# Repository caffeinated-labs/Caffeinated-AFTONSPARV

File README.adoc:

= Caffeinated AFTONSPARV

This small PCB replaces the original board inside your https://www.ikea.com/us/en/p/aftonsparv-led-decorative-light-planet-shape-multicolor-20559209/[AFTONSPARV Planet lamp].
It connects to your smart home setup via a common ESP32 firmware like https://esphome.io[esphome.io] or https://kno.wled.ge[WLED].

And the best thing, it's all OSHW certified: https://certification.oshwa.org/de000140.html[DE000140]

[#img-OSHW-DE000140,link=https://certification.oshwa.org/de000140.html]
image:docs/render.png[KiCad 3D render of the pcb, 500] image:docs/oshw.svg[OSHW-DE000140, 300]
image:docs/caffeinated-aftonsparv.jpg[Caffeinated AFTONSPARV, 850]

== Instructions

=== Step 1: Remove the cover
Remove the bottom cover from the AFTONSPARV lamp, there is no need to open the top cover. Open the marked screws, there's one under the sticker.

image:docs/step1.jpg[The bottom screws are highlited, 500]

=== Step 2: Disconnect the wires
Carefully de-solder all wires from the old board, it is not needed anymore.

image:docs/step2.jpg[Front of the lamp with the cover removed. The original pcb is visible, 500]

=== Step 3: Connect the PCB
Carefully solder the wires to the Caffeinated AFTONSPARV as shown below:

|===
| IKEA Lamp | PCB

|LED, black | LED R
|LED, green | LED G
|LED, transparent | LED B
|LED, white | LED {plus}

|Plug, white | POWER {plus}
|Plug, black | POWER -
|===
image:docs/pinout.png[LED and Power connections, 500]
image:docs/step3.jpg[All wires connected to the PCB, 500]

See <<PinOut>> for more details

=== Step 4: Test
Connect the power and test the PCB.
If nothing gets hot, you can measure 3.3V at the USB Port continue with the firmware installation

image:docs/step4.jpg[The PCB inside the lamp, 500]

=== Step 5: Install firmware
Connect the ESP to your computer using the TagConnect or USB interface and install the firmware of your choosing. The button on the front is connected to `IO9`, the boot-mode selectorfootnote:boot-mode[https://www.espressif.com/sites/default/files/documentation/esp32-c3-mini-1_datasheet_en.pdf#table.4].

IMPORTANT: The board *must* be powered with 24V to install firmware.

See <<Firmware>> and <<PinOut>> for more details

=== Step 6: Close it up
Carefully screw-on the cover and enjoy your new and _caffeinated_ lamp.

== PinOut

=== UART
NOTE: The diagram on the PCB v0.1 shows `IO8` - it is connected to `IO9`!

To upload software you can use the standard workflow using `esptool.py` footnote:esptool[https://docs.espressif.com/projects/esptool/en/latest/esp32/] just like any other ESP32 board. The UART interface is exposed on the TagConnect port:

image:docs/TagConnect.png[TagConnect location, 500] image:docs/TagConnect.svg[TagConnect pinout, 200]

It is recommended to use this https://github.com/Jana-Marie/USB-UART-BRIDGE[programmer from @Jana-Marie]

=== USB
In addition, the USB interface is exposed as well. It is located on the edge next to the 24V input. Please remember that the ESP32 uses 3.3V and *not* the usual 5V.

image:docs/USB-Interface.png[USB Interace, 500]

=== Boot Mode
The front button as well as the <<UART>> interface is connected to `IO9`, which is the boot mode selector (on older models `IO0`) on this ESP32footnote:boot-mode[]. Pressing the button or connecting it to ground puts the ESP into _Download Boot_ mode. Now you can install firmware via <<UART>> or <<USB>>

=== Power & LED
NOTE: On v0.1 the LEDs and Power connections are not labeled on the silkscreen.

Connect the AFTONSPARVs LEDs to the left ports as shown and the power input to the right most *big* connections, connecting to the USB Port will destroy the ESP.

image:docs/pinout.png[LED and Power connections, 500]

== Firmware
=== WLED
==== Installation
[%hardbreaks]
Installing the WLED firmware is easies with their web installer: https://install.wled.me/[install.wled.me]
When installing with `esptool` footnote:esptool[] follow this guide and use the ESP32-C3 binary: https://kno.wled.ge/basics/install-binary/[kno.wled.ge/basics/install-binary]
**Important:** Install this https://install.wled.me/bin/release_0_14_0/esp32-c3_bootloader_v2.bin[ESP32-C3 bootloader] *not* the ESP32 bootlader.

==== Configuration
[%hardbreaks]
LED Preferences > Hardware setup
*1*: `PWM RGB`
*Index*: `0`
*GPIOs*: `4`, `5`, `6`

*Button 0 GPIO*: `9`, `Pushbutton`

.Show screenshot
[%collapsible]
image:docs/wled.png[The above setting in the WLED interface, 400]

== Hardware

IMPORTANT: It is not possible to hand-solder this project, it requires a hot-air station or reflow oven. It is recommended to use a stencil for solder paste.

=== BOM

|===
| Reference         | Value                  | Qty | LCSC

|C1, C4, C7, C11    | 100nF                  | 4   | C14663
|C2                 | 100µF 35V              | 1   | C2831717
|C3, C6, C9, C10    | 4.7uF                  | 4   | C560882
|C5                 | 22pF                   | 1   | C105620
|L1                 | 10uH                   | 1   | C38117
|Q1-Q3              | AO3400A                | 3   | C347475
|R1-R3, R7-R10, R14 | 10kΩ                   | 8   | C98220
|R4-R6              | 20Ω                    | 3   | C22950
|R11                | 1Ω                     | 1   | C22936
|R12                | 100kΩ                  | 1   | C25803
|R13                | 22.1kΩ                 | 1   | C25961
|SW1                | SW_Push                | 1   | C2910748
|U1                 | ESP32-C3-MINI-1-[H/N]4 | 1   | C2934569 / C2838502
|U2                 | SY8201ABC              | 1   | C108052
|===

link:bom/ibom.html[BOM Tool]

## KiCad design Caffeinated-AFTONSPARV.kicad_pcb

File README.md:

# Caffeinated AFTONSPARV

This small PCB replaces the original board inside your [AFTONSPARV Planet lamp](https://www.ikea.com/us/en/p/aftonsparv-led-decorative-light-planet-shape-multicolor-20559209/).
You can connect it to your smart home using the ESP32 with common firmware. And the best thing, it's all OSHW certified: [DE000140](https://certification.oshwa.org/de000140.html)

## BOM
| Reference         | Value                  | Qty | LCSC                |
| ----------------- | ---------------------- | --- | ------------------- |
|C1, C4, C7, C11    | 100nF                  | 4   | C14663              |
|C2                 | 100µF 35V              | 1   | C2831717            |
|C3, C6, C9, C10    | 4.7uF                  | 4   | C560882             |
|C5                 | 22pF                   | 1   | C105620             |
|L1                 | 10uH                   | 1   | C38117              |
|Q1-Q3              | AO3400A                | 3   | C347475             |
|R1-R3, R7-R10, R14 | 10kΩ                   | 8   | C98220              |
|R4-R6              | 20Ω                    | 3   | C22950              |
|R11                | 1Ω                     | 1   | C22936              |
|R12                | 100kΩ                  | 1   | C25803              |
|R13                | 22.1kΩ                 | 1   | C25961              |
|SW1                | SW_Push                | 1   | C2910751            |
|U1                 | ESP32-C3-MINI-1-[H/N]4 | 1   | C2934569 / C2838502 |
|U2                 | SY8201ABC              | 1   | C108052             |

[BOM Tool](bom/ibom.html)

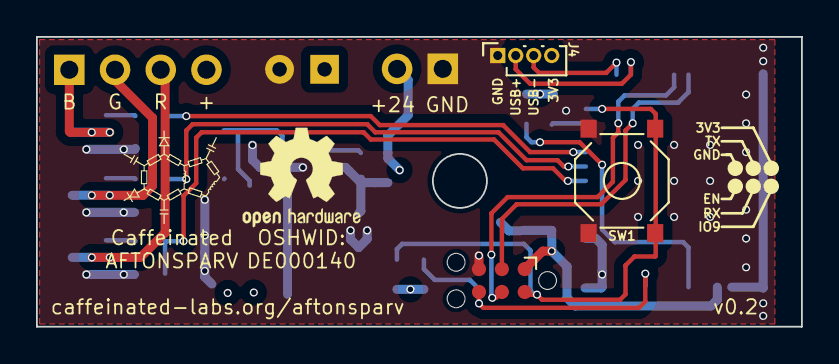
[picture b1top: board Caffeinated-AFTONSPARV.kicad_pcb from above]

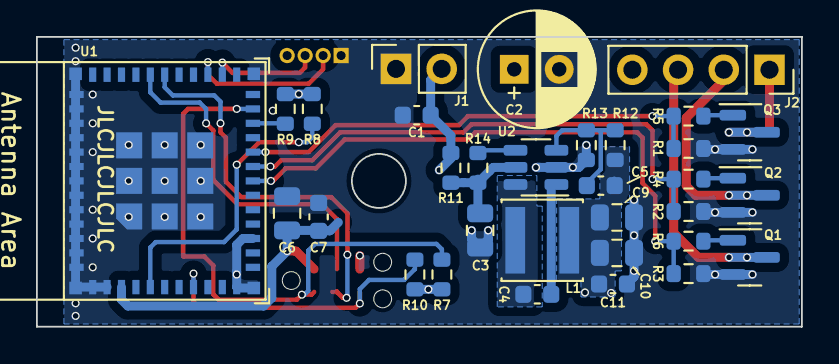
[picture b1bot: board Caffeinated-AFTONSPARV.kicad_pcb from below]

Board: 4 copper layers, 42.5 x 16.1 mm, 35 parts (32 on the bottom side), 25 nets.

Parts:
C1, C4, C7, C11: 100nF; C_0603_1608Metric
C2: 100µF 35V; CP_Radial_D6.3mm_P2.50mm
C3, C6, C9, C10: 4.7uF; C_0805_2012Metric
C5: 22pF; C_0603_1608Metric
J1: PWR; PinSocket_1x02_P2.54mm_Vertical
J2: LED; PinSocket_1x04_P2.54mm_Vertical
J3: TagConnect; Tag-Connect_TC2030-IDC-NL_2x03_P1.27mm_Vertical
J4: USB; PinSocket_1x04_P1.00mm_Vertical
L1: 10uH; L_Sunlord_SWPA4030S
Q1, Q2, Q3: AO3400A; SOT-23
R1, R2, R3, R7, R8, R9, R10, R14: 10kΩ; R_0603_1608Metric
R4, R5, R6: 20Ω; R_0603_1608Metric
R11: 1Ω; R_0603_1608Metric
R12: 100kΩ; R_0603_1608Metric
R13: 22.1kΩ; R_0603_1608Metric
SW1: SW_Push; YTS-C005
U1: ESP32-C3-MINI-1-[H/N]4; ESP32-C3-MINI-1
U2: SY8201ABC; SOT-23-6

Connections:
+3.3V: C5.2, C6.1, C7.1, C9.1, C10.1, C11.1, J3.1 (VCC), J4.4, L1.2, R7.1, R8.1, R9.1, R10.1, R12.1, U1.3 (3V3)
+24V: C1.1, C2.1, J1.2, J2.4, R11.1
EN: J3.6 (EN), R10.2, U1.8 (EN/CHIP_PU)
GND: C1.2, C2.2, C3.2, C6.2, C7.2, C9.2, C10.2, C11.2, J1.1, J3.5 (GND), J4.1, Q1.2 (S), Q2.2 (S), Q3.2 (S), R1.2, R2.2, R3.2, R13.2, SW1.1, U1.1 (GND), U1.2 (GND), U1.11 (GND), U1.14 (GND), U1.36 (GND), U1.37 (GND), U1.38 (GND), U1.39 (GND), U1.40 (GND), U1.41 (GND), U1.42 (GND), U1.43 (GND), U1.44 (GND), U1.45 (GND), U1.46 (GND), U1.47 (GND), U1.48 (GND), U1.49 (GND), U1.50 (GND), U1.51 (GND), U1.52 (GND), U1.53 (GND), U2.2 (GND)
IO9: J3.2 (IO0/IO9), R7.2, SW1.2, U1.23 (GPIO9)
LED-B: R1.1, R5.1, U1.20 (GPIO6)
LED-G: R2.1, R4.1, U1.19 (GPIO5/ADC2_CH0)
LED-R: R3.1, R6.1, U1.18 (GPIO4/ADC1_CH4)
unnamed: J2.1, Q3.3 (D)
unnamed: J2.2, Q2.3 (D)
unnamed: J2.3, Q1.3 (D)
unnamed: Q1.1 (G), R6.2
unnamed: Q2.1 (G), R4.2
unnamed: Q3.1 (G), R5.2
unnamed: R8.2, U1.5 (GPIO2/ADC1_CH2)
unnamed: R9.2, U1.22 (GPIO8)
unnamed: C4.2, U2.1 (BS)
unnamed: R14.2, U2.4 (EN)
unnamed: C5.1, R12.2, R13.1, U2.3 (FB)
unnamed: C3.1, R11.2, R14.1, U2.5 (IN)
unnamed: C4.1, L1.1, U2.6 (LX)
RX: J3.4 (RX), U1.30 (GPIO20/U0RXD)
TX: J3.3 (TX), U1.31 (GPIO21/U0TXD)
USB-D+: J4.2, U1.27 (GPIO19/USB_D+)
USB-D-: J4.3, U1.26 (GPIO18/USB_D-)

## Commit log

2023-10-09 feat(): Initial commit
2023-10-11 chore(): Add license
2023-10-11 feat(): Finalize design
2023-10-11 chore(gitignore): Add temporary files
2023-10-13 feat(): Rework pcb to 4 layers
2023-10-17 feat(): Rework and finalize design
2023-10-18 feat(): Replace L1 footprint and add Refs
2023-10-25 refactor(): Move vias
2023-10-29 docs(): Add README
2023-10-29 feat(pcb): Set drill pos and export settings
2023-10-29 feat(bom): Add ibom tool
2023-10-29 docs(): Add OSHW logo and link
2023-11-01 docs(): Update docs
2023-11-01 fix(silkscreen): Add labels to all connections, correct errors and bump number
2023-11-01 fix(3d-render): Hide connectors in the render
2023-11-08 docs(): Update docs with pictures and installation instructions
2023-11-10 feat(): Update silkscreen, ibom, use smaller sw
2023-11-10 docs(): Add link to recommended programmer
